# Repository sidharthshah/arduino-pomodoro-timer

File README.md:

Simple Pomodoro Timer build with Custom PCB. Find Arduino sketch in arduino folder

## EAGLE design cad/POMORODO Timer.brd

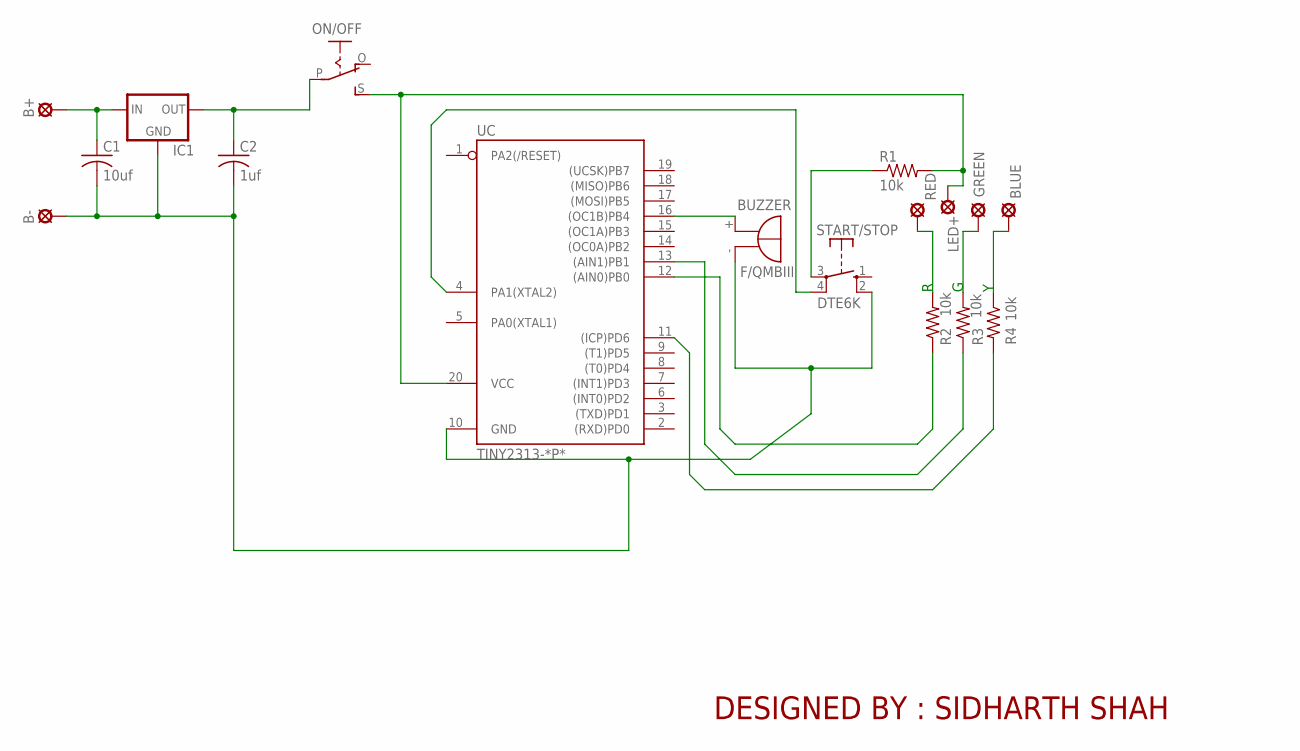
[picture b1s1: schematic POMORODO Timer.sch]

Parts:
B+: SE14
B-: SE14
BLUE: SE14
BUZZER: F/QMBIII
C1: 10uf; C025-025X050
C2: 1uf; C025-025X050
GREEN: SE14
IC1: 7805; TO220LV
LED+: SE14
ON/OFF: EG1218S; EG1218
R1, R2, R3, R4: 10k; 0207/10
RED: SE14
START/STOP: DTE6K
UC: TINY2313-*P*; DIL20

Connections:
GND: B-.MP, BUZZER.- (+), C1.2, C2.2, IC1.2 (GND), START/STOP.2 (S), UC.10 (GND)
INPUT: START/STOP.4, UC.4 (PA1(XTAL2))
unnamed: R2.2, RED.MP
unnamed: GREEN.MP, R3.2
unnamed: BLUE.MP, R4.1
unnamed: R2.1, UC.12 ((AIN0)PB0)
unnamed: R3.1, UC.13 ((AIN1)PB1)
unnamed: R1.1, START/STOP.3
unnamed: BUZZER.+ (-), UC.16 ((OC1B)PB4)
unnamed: C2.1, IC1.3 (OUT), ON/OFF.P
unnamed: R4.2, UC.11 ((ICP)PD6)
unnamed: LED+.MP, ON/OFF.S, R1.2, UC.20 (VCC)
unnamed: B+.MP, C1.1, IC1.1 (IN)

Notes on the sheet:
DESIGNED BY : SIDHARTH SHAH

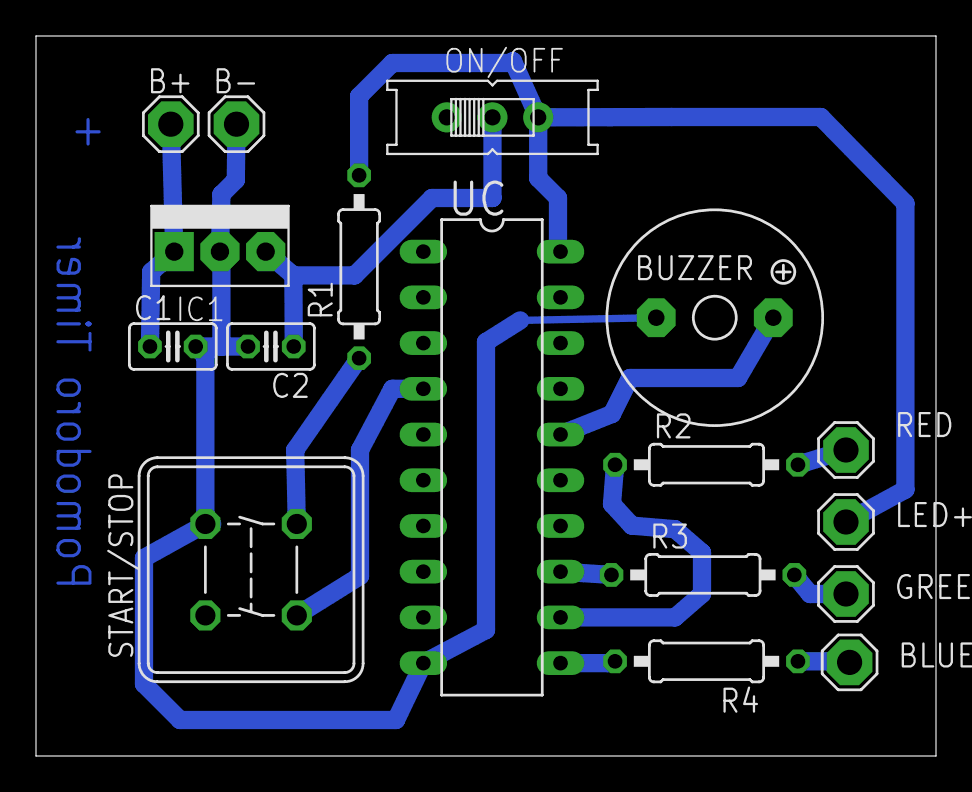
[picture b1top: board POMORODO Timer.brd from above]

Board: 2 copper layers, 50.0 x 40.0 mm, 17 parts (0 on the bottom side), 13 nets.
